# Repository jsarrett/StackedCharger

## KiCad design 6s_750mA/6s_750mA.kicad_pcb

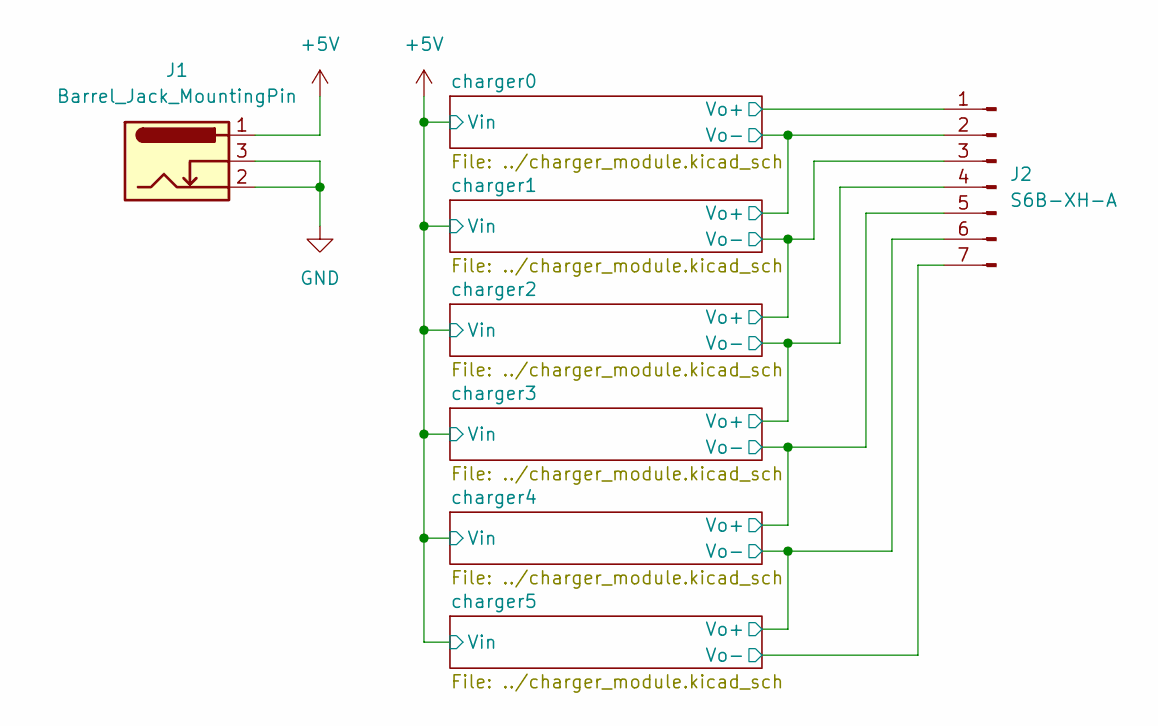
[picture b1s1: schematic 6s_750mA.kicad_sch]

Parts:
J1: Barrel_Jack_MountingPin; BarrelJack_CUI_PJ-102AH_Horizontal; Manufacturer Part Number PJ-102AH
J2: S6B-XH-A; JST_XH_S7B-XH-A_1x07_P2.50mm_Horizontal; Manufacturer Part Number S7B-XH-A

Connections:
+5V: J1.1; also elsewhere on the board
/charger0/Vo+: J2.1; also elsewhere on the board
/charger0/Vo-: J2.2; also elsewhere on the board
/charger1/Vo-: J2.3; also elsewhere on the board
/charger2/Vo-: J2.4; also elsewhere on the board
/charger3/Vo-: J2.5; also elsewhere on the board
/charger4/Vo-: J2.6; also elsewhere on the board
/charger5/Vo-: J2.7; also elsewhere on the board
GND: J1.2, J1.3; also elsewhere on the board

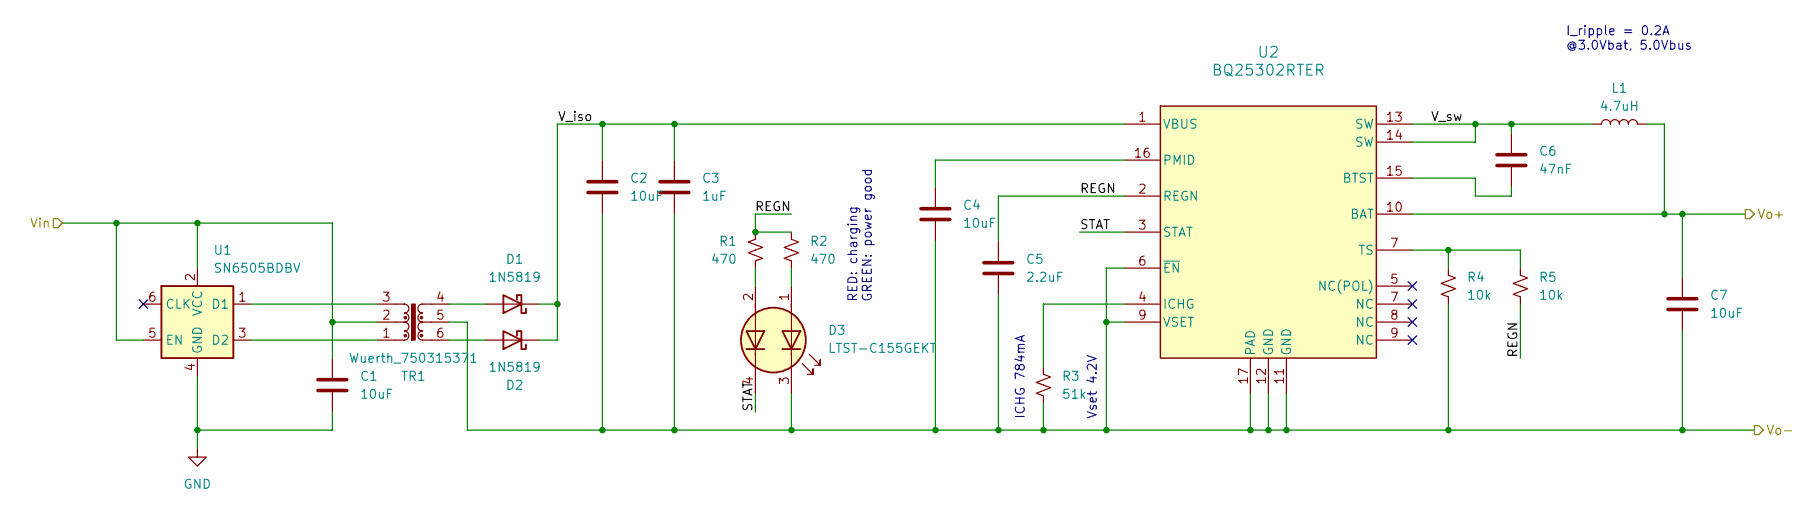
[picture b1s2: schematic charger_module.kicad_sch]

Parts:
C1, C2: 10uF; C_0805_2012Metric; Manufacturer Part Number CL21A106MQFNNNE
C3: 1uF; C_0603_1608Metric; Manufacturer Part Number CC0603KRX7R7BB105
C4, C7: 10uF; C_0603_1608Metric; Manufacturer Part Number CL10A106KQ8NNNL
C5: 2.2uF; C_0603_1608Metric; Manufacturer Part Number CL10A225KQ8NNNC
C6: 47nF; C_0603_1608Metric; Manufacturer Part Number CL10B473KO8NNNC
D1, D2: 1N5819; D_SOD-123F; Manufacturer Part Number 1N5819W
D3: LTST-C155GEKT; LED_RGB_Wuerth-PLCC4_3.2x2.8mm_150141M173100; Manufacturer Part Number LTST-C155GEKT
L1: 4.7uH; L_0805_2012Metric_Pad1.15x1.40mm_HandSolder; Manufacturer Part Number WIP201610S-4R7MLDG
R1, R2: 470; R_0603_1608Metric; Manufacturer Part Number RT0603FRE07470RL
R3: 51k; R_0603_1608Metric; Manufacturer Part Number RT0603FRE0751KL
R4, R5: 10k; R_0603_1608Metric; Manufacturer Part Number RT0603FRE0710KL
TR1: Wuerth_750315371; Transformer_Wuerth_750315371; Manufacturer Part Number 750315371
U1: SN6505BDBV; SOT-23-6; Manufacturer Part Number SN6505BDBV
U2: BQ25302RTER; RTE0016C; Manufacturer Part Number BQ25302RTER

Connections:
+5V: C1.1, TR1.2, U1.2 (VCC), U1.5 (EN); also elsewhere on the board
/charger0/REGN: C5.1, R1.1, R2.1, R5.2, U2.2 (REGN)
/charger0/STAT: D3.4 (K2), U2.3 (STAT)
/charger0/V_iso: C2.1, C3.1, D1.1 (K), D2.1 (K), U2.1 (VBUS)
/charger0/V_sw: C6.1, L1.1, U2.13 (SW), U2.14 (SW)
/charger0/Vo+: C7.1, L1.2, U2.10 (BAT); also elsewhere on the board
/charger0/Vo-: C2.2, C3.2, C4.2, C5.2, C7.2, D3.3 (K1), R3.2, R4.2, TR1.5, U2.6 (~EN), U2.9 (VSET), U2.11 (GND), U2.12 (GND), U2.17 (PAD); also elsewhere on the board
GND: C1.2, U1.4 (GND); also elsewhere on the board
unnamed: D1.2 (A), TR1.4
unnamed: D2.2 (A), TR1.6
unnamed: D3.1 (A1), R2.2
unnamed: D3.2 (A2), R1.2
unnamed: TR1.3, U1.1 (D1)
unnamed: TR1.1, U1.3 (D2)
unnamed: C6.2, U2.15 (BTST)
unnamed: R3.1, U2.4 (ICHG)
unnamed: C4.1, U2.16 (PMID)
unnamed: R4.1, R5.1, U2.7 (TS)

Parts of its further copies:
C8, C9, C15, C16, C22, C23, C29, C30, C36, C37: 10uF; C_0805_2012Metric; Manufacturer Part Number CL21A106MQFNNNE
C10, C17, C24, C31, C38: 1uF; C_0603_1608Metric; Manufacturer Part Number CC0603KRX7R7BB105
C11, C14, C18, C21, C25, C28, C32, C35, C39, C42: 10uF; C_0603_1608Metric; Manufacturer Part Number CL10A106KQ8NNNL
C12, C19, C26, C33, C40: 2.2uF; C_0603_1608Metric; Manufacturer Part Number CL10A225KQ8NNNC
C13, C20, C27, C34, C41: 47nF; C_0603_1608Metric; Manufacturer Part Number CL10B473KO8NNNC
D4, D5, D7, D8, D10, D11, D13, D14, D16, D17: 1N5819; D_SOD-123F; Manufacturer Part Number 1N5819W
D6, D9, D12, D15, D18: LTST-C155GEKT; LED_RGB_Wuerth-PLCC4_3.2x2.8mm_150141M173100; Manufacturer Part Number LTST-C155GEKT
L2, L3, L4, L5, L6: 4.7uH; L_0805_2012Metric_Pad1.15x1.40mm_HandSolder; Manufacturer Part Number WIP201610S-4R7MLDG
R6, R7, R11, R12, R16, R17, R21, R22, R26, R27: 470; R_0603_1608Metric; Manufacturer Part Number RT0603FRE07470RL
R8, R13, R18, R23, R28: 51k; R_0603_1608Metric; Manufacturer Part Number RT0603FRE0751KL
R9, R10, R14, R15, R19, R20, R24, R25, R29, R30: 10k; R_0603_1608Metric; Manufacturer Part Number RT0603FRE0710KL
TR2, TR3, TR4, TR5, TR6: Wuerth_750315371; Transformer_Wuerth_750315371; Manufacturer Part Number 750315371
U3, U5, U7, U9, U11: SN6505BDBV; SOT-23-6; Manufacturer Part Number SN6505BDBV
U4, U6, U8, U10, U12: BQ25302RTER; RTE0016C; Manufacturer Part Number BQ25302RTER

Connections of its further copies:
+5V: C8.1, C15.1, C22.1, C29.1, C36.1, TR2.2, TR3.2, TR4.2, TR5.2, TR6.2, U3.2 (VCC), U3.5 (EN), U5.2 (VCC), U5.5 (EN), U7.2 (VCC), U7.5 (EN), U9.2 (VCC), U9.5 (EN), U11.2 (VCC), U11.5 (EN); also elsewhere on the board
/charger0/Vo-: C14.1, L2.2, U4.10 (BAT); also elsewhere on the board
/charger1/REGN: C12.1, R6.1, R7.1, R10.2, U4.2 (REGN)
/charger1/STAT: D6.4 (K2), U4.3 (STAT)
/charger1/V_iso: C9.1, C10.1, D4.1 (K), D5.1 (K), U4.1 (VBUS)
/charger1/V_sw: C13.1, L2.1, U4.13 (SW), U4.14 (SW)
/charger1/Vo-: C9.2, C10.2, C11.2, C12.2, C14.2, C21.1, D6.3 (K1), L3.2, R8.2, R9.2, TR2.5, U4.6 (~EN), U4.9 (VSET), U4.11 (GND), U4.12 (GND), U4.17 (PAD), U6.10 (BAT); also elsewhere on the board
/charger2/REGN: C19.1, R11.1, R12.1, R15.2, U6.2 (REGN)
/charger2/STAT: D9.4 (K2), U6.3 (STAT)
/charger2/V_iso: C16.1, C17.1, D7.1 (K), D8.1 (K), U6.1 (VBUS)
/charger2/V_sw: C20.1, L3.1, U6.13 (SW), U6.14 (SW)
/charger2/Vo-: C16.2, C17.2, C18.2, C19.2, C21.2, C28.1, D9.3 (K1), L4.2, R13.2, R14.2, TR3.5, U6.6 (~EN), U6.9 (VSET), U6.11 (GND), U6.12 (GND), U6.17 (PAD), U8.10 (BAT); also elsewhere on the board
/charger3/REGN: C26.1, R16.1, R17.1, R20.2, U8.2 (REGN)
/charger3/STAT: D12.4 (K2), U8.3 (STAT)
/charger3/V_iso: C23.1, C24.1, D10.1 (K), D11.1 (K), U8.1 (VBUS)
/charger3/V_sw: C27.1, L4.1, U8.13 (SW), U8.14 (SW)
/charger3/Vo-: C23.2, C24.2, C25.2, C26.2, C28.2, C35.1, D12.3 (K1), L5.2, R18.2, R19.2, TR4.5, U8.6 (~EN), U8.9 (VSET), U8.11 (GND), U8.12 (GND), U8.17 (PAD), U10.10 (BAT); also elsewhere on the board
/charger4/REGN: C33.1, R21.1, R22.1, R25.2, U10.2 (REGN)
/charger4/STAT: D15.4 (K2), U10.3 (STAT)
/charger4/V_iso: C30.1, C31.1, D13.1 (K), D14.1 (K), U10.1 (VBUS)
/charger4/V_sw: C34.1, L5.1, U10.13 (SW), U10.14 (SW)
/charger4/Vo-: C30.2, C31.2, C32.2, C33.2, C35.2, C42.1, D15.3 (K1), L6.2, R23.2, R24.2, TR5.5, U10.6 (~EN), U10.9 (VSET), U10.11 (GND), U10.12 (GND), U10.17 (PAD), U12.10 (BAT); also elsewhere on the board
/charger5/REGN: C40.1, R26.1, R27.1, R30.2, U12.2 (REGN)
/charger5/STAT: D18.4 (K2), U12.3 (STAT)
/charger5/V_iso: C37.1, C38.1, D16.1 (K), D17.1 (K), U12.1 (VBUS)
/charger5/V_sw: C41.1, L6.1, U12.13 (SW), U12.14 (SW)
/charger5/Vo-: C37.2, C38.2, C39.2, C40.2, C42.2, D18.3 (K1), R28.2, R29.2, TR6.5, U12.6 (~EN), U12.9 (VSET), U12.11 (GND), U12.12 (GND), U12.17 (PAD); also elsewhere on the board
GND: C8.2, C15.2, C22.2, C29.2, C36.2, U3.4 (GND), U5.4 (GND), U7.4 (GND), U9.4 (GND), U11.4 (GND); also elsewhere on the board
unnamed: D4.2 (A), TR2.4
unnamed: D5.2 (A), TR2.6
unnamed: D6.1 (A1), R7.2
unnamed: D6.2 (A2), R6.2
unnamed: D7.2 (A), TR3.4
unnamed: D8.2 (A), TR3.6
unnamed: D9.1 (A1), R12.2
unnamed: D9.2 (A2), R11.2
unnamed: D10.2 (A), TR4.4
unnamed: D11.2 (A), TR4.6
unnamed: D12.1 (A1), R17.2
unnamed: D12.2 (A2), R16.2
unnamed: D13.2 (A), TR5.4
unnamed: D14.2 (A), TR5.6
unnamed: D15.1 (A1), R22.2
unnamed: D15.2 (A2), R21.2
unnamed: D16.2 (A), TR6.4
unnamed: D17.2 (A), TR6.6
unnamed: D18.1 (A1), R27.2
unnamed: D18.2 (A2), R26.2
unnamed: TR2.3, U3.1 (D1)
unnamed: TR2.1, U3.3 (D2)
unnamed: C13.2, U4.15 (BTST)
unnamed: R8.1, U4.4 (ICHG)
unnamed: C11.1, U4.16 (PMID)
unnamed: R9.1, R10.1, U4.7 (TS)
unnamed: TR3.3, U5.1 (D1)
unnamed: TR3.1, U5.3 (D2)
unnamed: C20.2, U6.15 (BTST)
unnamed: R13.1, U6.4 (ICHG)
unnamed: C18.1, U6.16 (PMID)
unnamed: R14.1, R15.1, U6.7 (TS)
unnamed: TR4.3, U7.1 (D1)
unnamed: TR4.1, U7.3 (D2)
unnamed: C27.2, U8.15 (BTST)
unnamed: R18.1, U8.4 (ICHG)
unnamed: C25.1, U8.16 (PMID)
unnamed: R19.1, R20.1, U8.7 (TS)
unnamed: TR5.3, U9.1 (D1)
unnamed: TR5.1, U9.3 (D2)
unnamed: C34.2, U10.15 (BTST)
unnamed: R23.1, U10.4 (ICHG)
unnamed: C32.1, U10.16 (PMID)
unnamed: R24.1, R25.1, U10.7 (TS)
unnamed: TR6.3, U11.1 (D1)
unnamed: TR6.1, U11.3 (D2)
unnamed: C41.2, U12.15 (BTST)
unnamed: R28.1, U12.4 (ICHG)
unnamed: C39.1, U12.16 (PMID)
unnamed: R29.1, R30.1, U12.7 (TS)

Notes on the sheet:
I_ripple = 0.2A @3.0Vbat, 5.0Vbus
ICHG 784mA
RED: charging GREEN: power good
Vset 4.2V

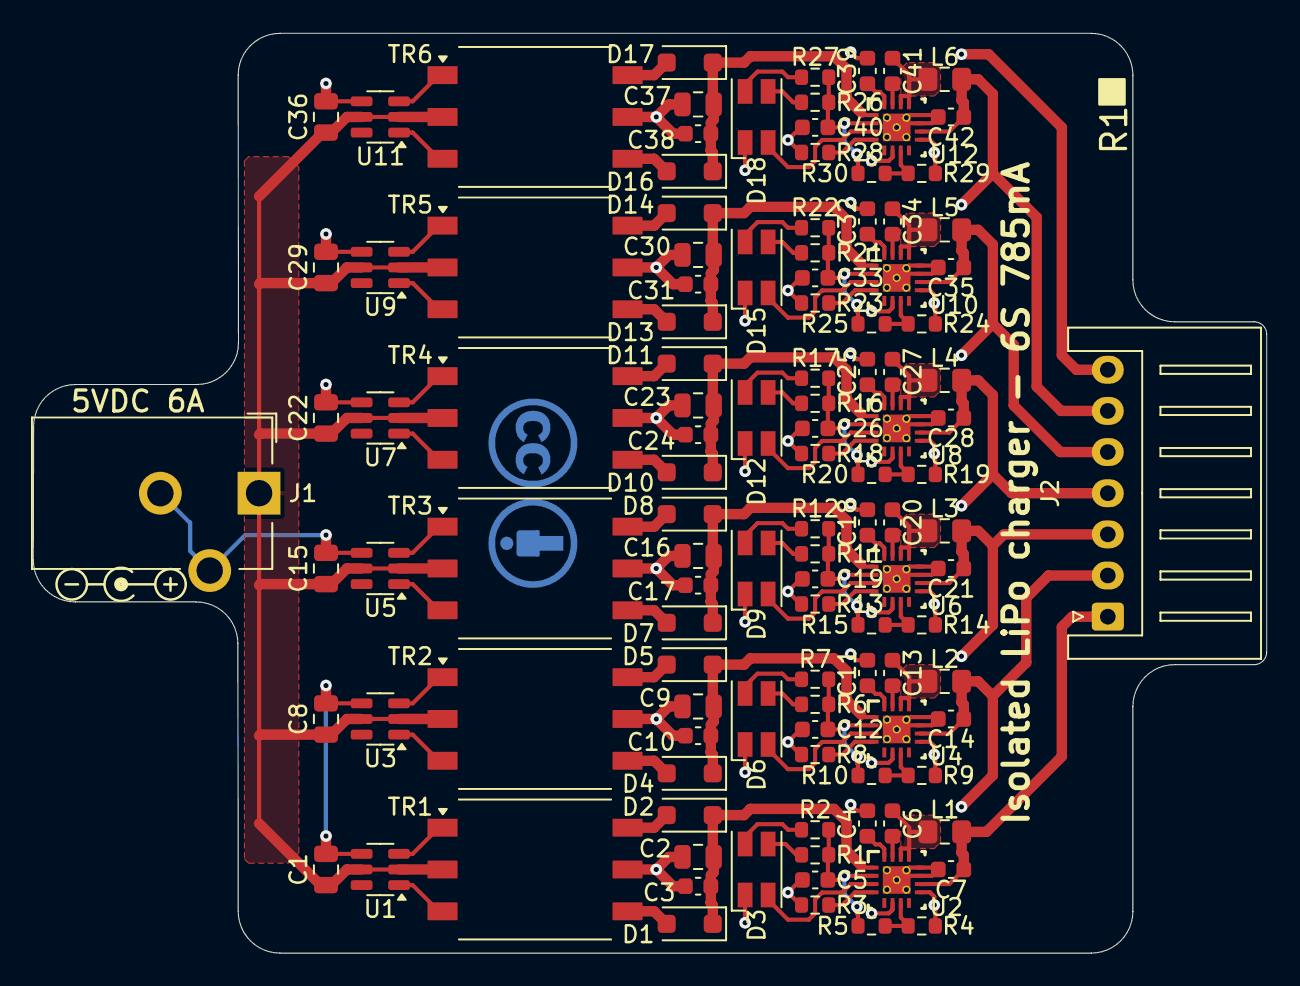
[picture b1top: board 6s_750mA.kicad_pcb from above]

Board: 2 copper layers, 74.9 x 55.9 mm, 116 parts (0 on the bottom side), 93 nets.

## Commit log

2024-07-23 isolated charger module schematic
2024-07-23 6s charger schematic
2024-07-23 initial layout
2024-07-23 ignore lock files
2024-07-23 add logos and CC icons to bottom
2024-07-23 extend ground pour and use thermal reliefs for easier soldering
2024-07-23 fix 3d model for charge controller
2024-07-24 6s R0 DFM checked
2024-07-24 6s R0 out to fab
2024-08-01 fix color assignment on status LEDs
2024-08-01 fix supplier part numbers for power connector and battery connector
2024-08-01 update PCB with correct LED colors, and fix typo
2024-08-13 Add BQ25302 part to library
2024-08-13 switch to BQ25302 charger IC instead of LDO
2024-08-13 new layout using switching regulator
2024-08-13 production files for 6s_750mA R1

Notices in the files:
6s_750mA/6s_750mA.kicad_pcb:
©2024 by James Sarrett
licensed under CC BY 4.0
